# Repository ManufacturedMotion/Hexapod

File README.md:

# Hex

Hex is a six legged OpenSource Hexapod designed to serve as a moving platform for you to tinker with and build on top of! We are currently working on the third generation of the platform, Hex3.

If you're interested in learning more about the project, [visit our wiki!](https://github.com/ManufacturedMotion/Hexapod/wiki). If you want to build your own or join the community, check out our [Hex Discord](https://discord.gg/v3bbvRtFUr).

To find out info on what we're planning to change, [checkout our GitHub issues!](https://github.com/ManufacturedMotion/Hexapod/issues).

## Generations

### Hex1

- [Overview](https://github.com/ManufacturedMotion/Hexapod/wiki#mk1)
- Completed: July 2023 - May 2024
- MIT LICENSE

### Hex2
- [Overview](https://github.com/ManufacturedMotion/Hexapod/wiki#mk2)
- Completed: May 2024 - July 2025
- MIT LICENSE

### Hex3
- In-Progress: July 2025 - Present
- GNU GENERAL PUBLIC LICENSE V3

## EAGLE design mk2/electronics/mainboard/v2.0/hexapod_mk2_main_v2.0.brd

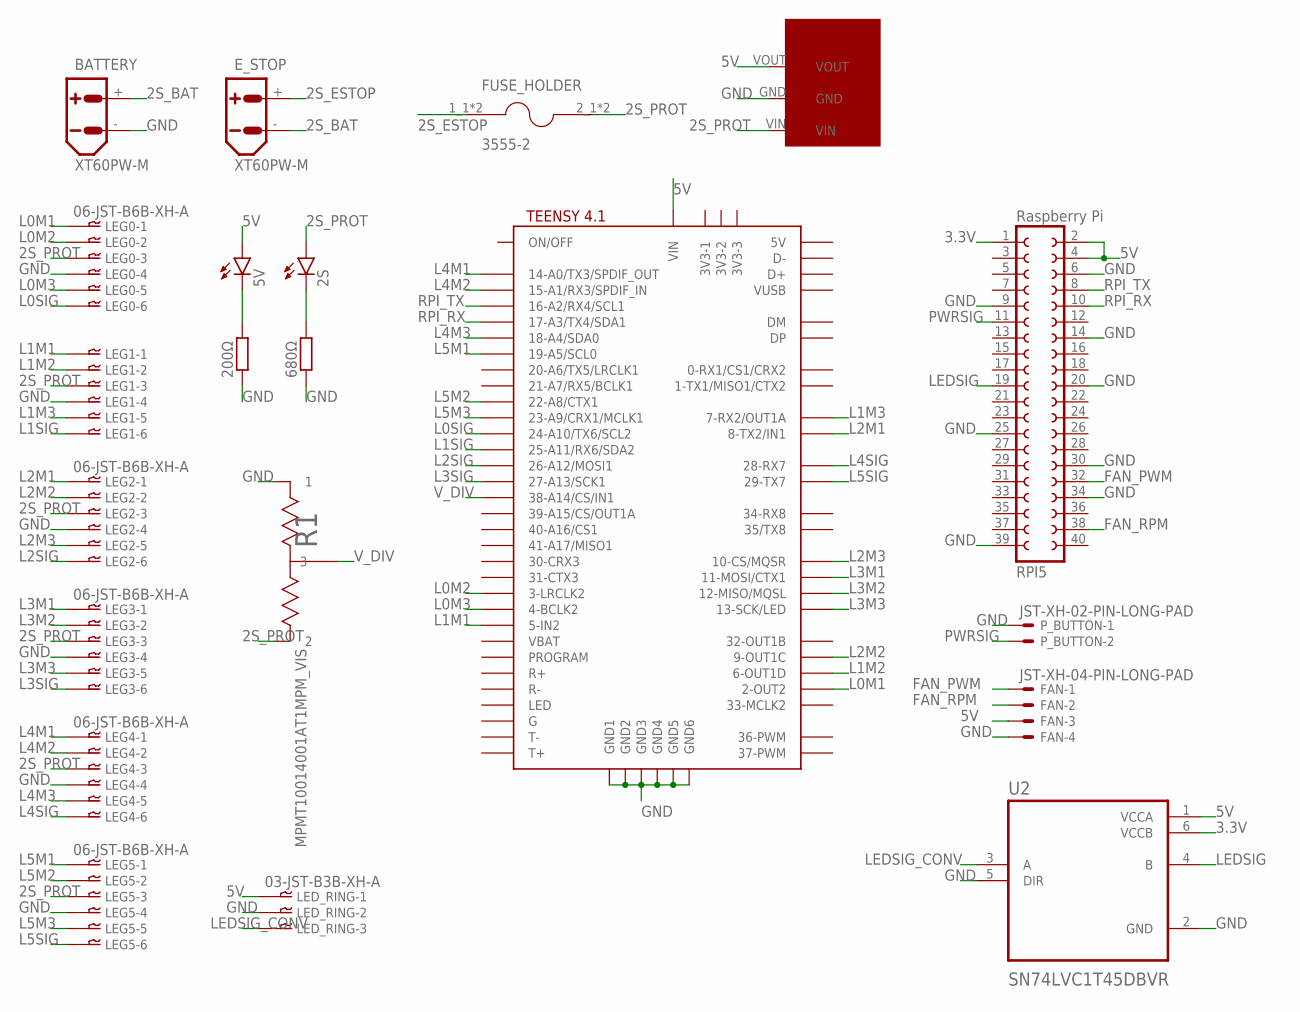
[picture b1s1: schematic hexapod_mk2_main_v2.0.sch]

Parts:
2S, 5V: LEDCHIPLED_0805; CHIPLED_0805
200Ω, 680Ω: R-EU_R0805; R0805
BATTERY: XT60PW-M
DFR0753: DFR0753
E_STOP: XT60PW-M
FAN: JST-XH-04-PIN-LONG-PAD; JST-XH-04-PACKAGE-LONG-PAD
FUSE_HOLDER: 3555-2; FUSE_3555-2
LED_RING: 03-JST-B3B-XH-A; B3B-XH
LEG0, LEG1, LEG2, LEG3, LEG4, LEG5: 06-JST-B6B-XH-A; B6B-XH
P_BUTTON: JST-XH-02-PIN-LONG-PAD; JST-XH-02-PACKAGE-LONG-PAD
R1: MPMT10014001AT1MPM_VIS; MPM_VIS
RPI5: Raspberry Pi; FE20-2
U2: SN74LVC1T45DBVR; SOT95P280X145-6N
U$1: TEENSY41

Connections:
2S_BAT: BATTERY.+, E_STOP.-
2S_ESTOP: E_STOP.+, FUSE_HOLDER.1_1 (1), FUSE_HOLDER.1_2 (1)
2S_PROT: 2S.A, DFR0753.VIN, FUSE_HOLDER.2_1 (2), FUSE_HOLDER.2_2 (2), LEG0.P$3, LEG1.P$3, LEG2.P$3, LEG3.P$3, LEG4.P$3, LEG5.P$3, R1.2
3.3V: RPI5.1, U2.6 (VCCB)
5V: 5V.A, DFR0753.VOUT, FAN.3, LED_RING.P$1, RPI5.2, RPI5.4, U2.1 (VCCA), U$1.VIN
FAN_PWM: FAN.1, RPI5.32
FAN_RPM: FAN.2, RPI5.38
GND: 200Ω.1, 680Ω.1, BATTERY.-, DFR0753.GND, FAN.4, LED_RING.P$2, LEG0.P$4, LEG1.P$4, LEG2.P$4, LEG3.P$4, LEG4.P$4, LEG5.P$4, P_BUTTON.1, R1.1, RPI5.6, RPI5.9, RPI5.14, RPI5.20, RPI5.25, RPI5.30, RPI5.34, RPI5.39, U2.2 (GND), U2.5 (DIR), U$1.GND1, U$1.GND2, U$1.GND3, U$1.GND4, U$1.GND5, U$1.GND6
L0M1: LEG0.P$1, U$1.2-OUT2
L0M2: LEG0.P$2, U$1.3-LRCLK2
L0M3: LEG0.P$5, U$1.4-BCLK2
L0SIG: LEG0.P$6, U$1.24-A10/TX6/SCL2
L1M1: LEG1.P$1, U$1.5-IN2
L1M2: LEG1.P$2, U$1.6-OUT1D
L1M3: LEG1.P$5, U$1.7-RX2/OUT1A
L1SIG: LEG1.P$6, U$1.25-A11/RX6/SDA2
L2M1: LEG2.P$1, U$1.8-TX2/IN2 (8-TX2/IN1)
L2M2: LEG2.P$2, U$1.9-OUT1C
L2M3: LEG2.P$5, U$1.10-CS\MQSR (10-CS/MQSR)
L2SIG: LEG2.P$6, U$1.26-A12/MOSI1
L3M1: LEG3.P$1, U$1.11-MOSI/CTX1
L3M2: LEG3.P$2, U$1.12-MISO/MQSL
L3M3: LEG3.P$5, U$1.13-SCK/LED
L3SIG: LEG3.P$6, U$1.27-A13/SCK1
L4M1: LEG4.P$1, U$1.14-A0/TX3/SPDIF_OUT
L4M2: LEG4.P$2, U$1.15-A1/RX3/SPDIF_IN
L4M3: LEG4.P$5, U$1.18-A4/SDA0
L4SIG: LEG4.P$6, U$1.28-RX7
L5M1: LEG5.P$1, U$1.19-A5/SCL0
L5M2: LEG5.P$2, U$1.22-A8/CTX1
L5M3: LEG5.P$5, U$1.23-A9/CRX1/MCLK1
L5SIG: LEG5.P$6, U$1.29-TX7
LEDSIG: RPI5.19, U2.4 (B)
LEDSIG_CONV: LED_RING.P$3, U2.3 (A)
unnamed: 5V.C, 200Ω.2
unnamed: 2S.C, 680Ω.2
PWRSIG: P_BUTTON.2, RPI5.11
RPI_RX: RPI5.10, U$1.17-A3/TX4/SDA1
RPI_TX: RPI5.8, U$1.16-A2/RX4/SCL1
V_DIV: R1.3, U$1.38-A14/CS/IN1

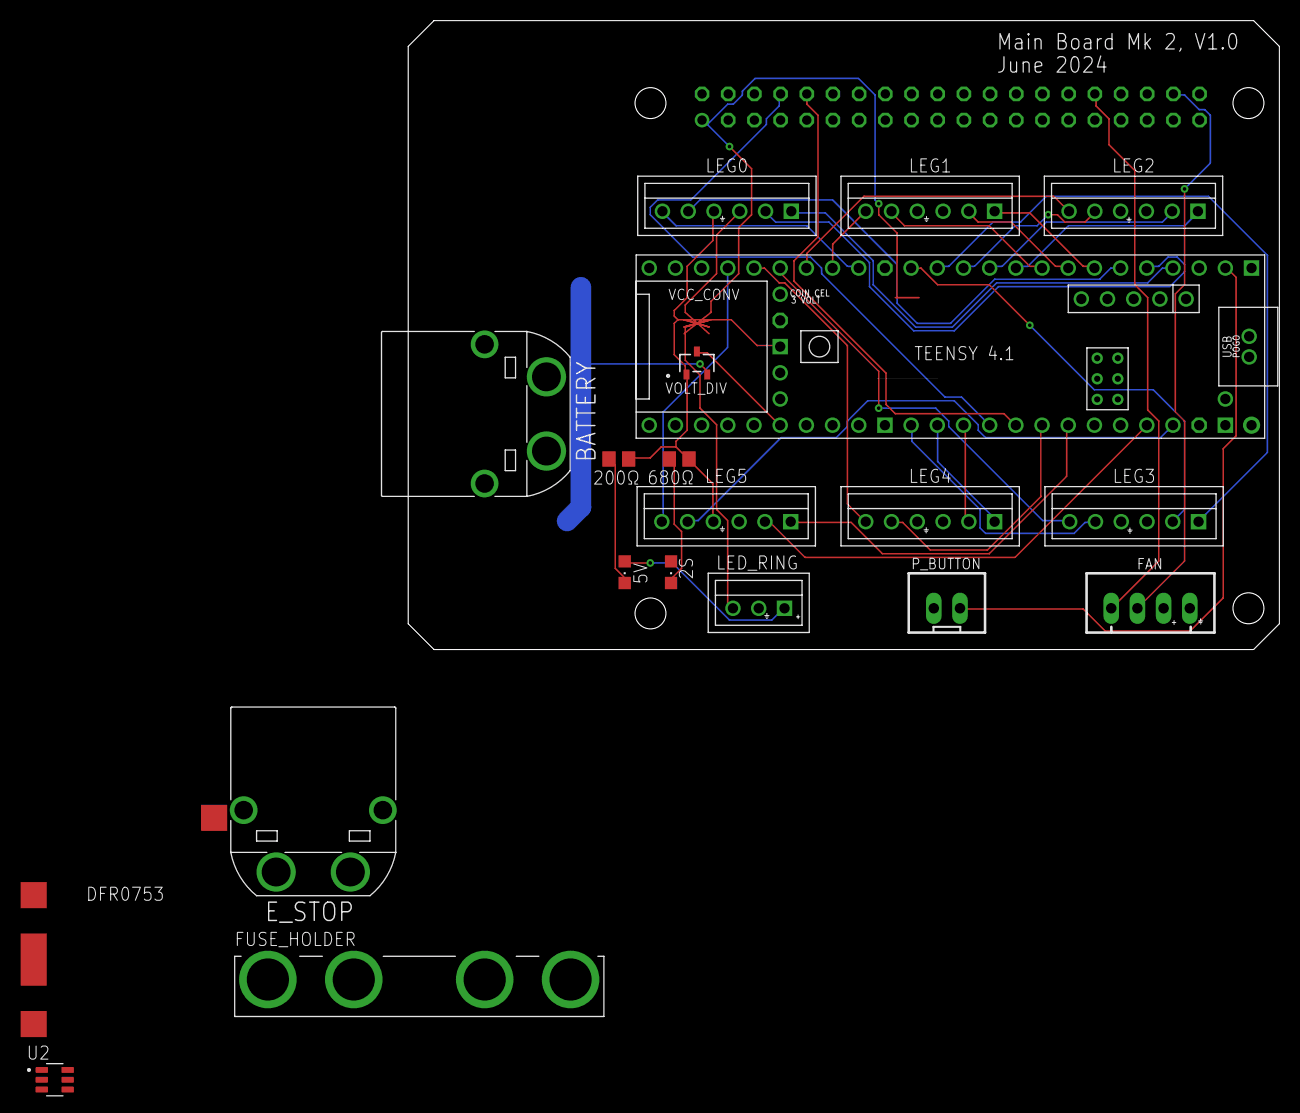
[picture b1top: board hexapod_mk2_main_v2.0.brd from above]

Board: 4 copper layers, 84.5 x 61.0 mm, 21 parts (1 on the bottom side), 40 nets.

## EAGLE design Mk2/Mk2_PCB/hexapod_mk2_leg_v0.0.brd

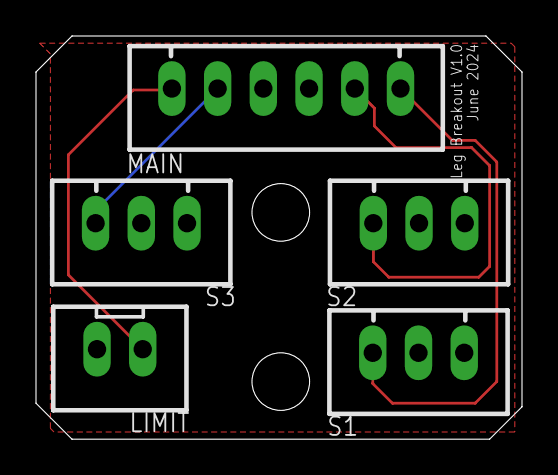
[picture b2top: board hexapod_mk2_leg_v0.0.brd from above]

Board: 2 copper layers, 27.0 x 22.4 mm, 5 parts (0 on the bottom side), 6 nets.

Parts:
LIMIT: JST-XH-02-PIN-LONG-PAD; JST-XH-02-PACKAGE-LONG-PAD
MAIN: JST-XH-06-PIN-LONG-PAD; JST-XH-06-PACKAGE-LONG-PAD
S1, S2, S3: JST-XH-03-PIN-LONG-PAD; JST-XH-03-PACKAGE-LONG-PAD

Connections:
5V: MAIN.3, S1.2, S2.2, S3.2
GND: LIMIT.2, MAIN.4, S1.1, S2.1, S3.1
LIMIT: LIMIT.1, MAIN.6
S1SIG: MAIN.1, S1.3
S2SIG: MAIN.2, S2.3
S3SIG: MAIN.5, S3.3

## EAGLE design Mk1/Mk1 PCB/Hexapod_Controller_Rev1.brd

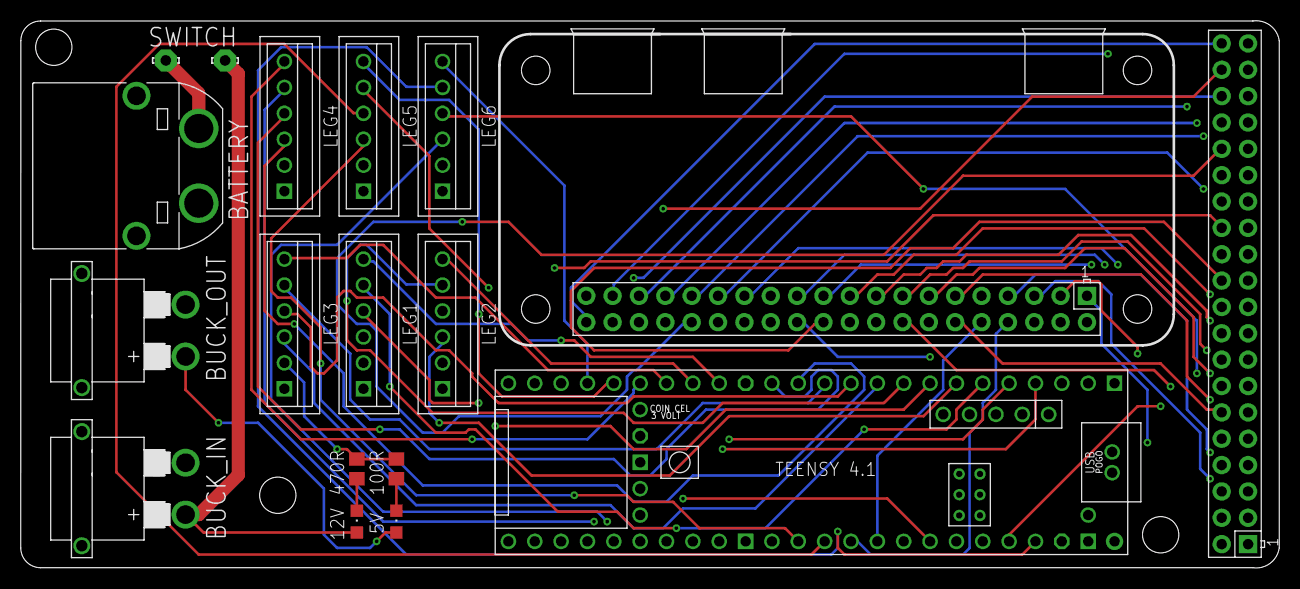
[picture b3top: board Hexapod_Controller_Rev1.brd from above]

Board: 4 copper layers, 121.3 x 52.7 mm, 18 parts (0 on the bottom side), 60 nets.

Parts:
5V, 12V: CHIPLED_0805
100R, 470R: R0805
BATTERY: XT60PW-M
BUCK_IN: XT30PW-M
BUCK_OUT: XT30PW-M
LEG1, LEG2, LEG3, LEG4, LEG5, LEG6: 06-JST-B6B-XH-A; B6B-XH
LSP1, LSP2: LSP10
U$1: TEENSY41
U$2, U$3: RPI-ZERO; RASPBERRYPI_BASTELSTUBE_V13_RASPI_BOARD_B+_FULL

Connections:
3V3: U$2.1, U$3.1
3V3_2: U$2.17, U$3.17
5V: 5V.A, BUCK_OUT.+, LEG1.P$1, LEG2.P$1, LEG3.P$1, LEG4.P$1, LEG5.P$1, LEG6.P$1, U$1.VIN, U$2.2, U$2.4, U$3.2, U$3.4
12V: 12V.A, BUCK_IN.+, LSP2.MP
12V_PRE: BATTERY.+, LSP1.MP
GND: 100R.1, 470R.1, BATTERY.-, BUCK_IN.-, BUCK_OUT.-, LEG1.P$2, LEG2.P$2, LEG3.P$2, LEG4.P$2, LEG5.P$2, LEG6.P$2, U$1.GND1, U$1.GND2, U$1.GND3, U$1.GND4, U$1.GND5, U$1.GND6, U$2.6, U$2.9, U$2.14, U$2.20, U$2.25, U$2.30, U$2.34, U$2.39, U$3.6, U$3.9, U$3.14, U$3.20, U$3.25, U$3.30, U$3.34, U$3.39
GPIO2: U$2.3, U$3.3
GPIO3: U$2.5, U$3.5
GPIO4: U$2.7, U$3.7
GPIO5: U$2.29, U$3.29
GPIO6: U$2.31, U$3.31
GPIO7: U$2.26, U$3.26
GPIO8: U$2.24, U$3.24
GPIO9: U$2.21, U$3.21
GPIO10: U$2.19, U$3.19
GPIO11: U$2.23, U$3.23
GPIO12: U$2.32, U$3.32
GPIO13: U$2.33, U$3.33
GPIO16: U$2.36, U$3.36
GPIO17: U$2.11, U$3.11
GPIO18: U$2.12, U$3.12
GPIO19: U$2.35, U$3.35
GPIO20: U$2.38, U$3.38
GPIO21: U$2.40, U$3.40
GPIO22: U$2.15, U$3.15
GPIO23: U$2.16, U$3.16
GPIO24: U$2.18, U$3.18
GPIO25: U$2.22, U$3.22
GPIO26: U$2.37, U$3.37
GPIO27: U$2.13, U$3.13
ID_SC: U$2.28, U$3.28
ID_SD: U$2.27, U$3.27
L1M1: LEG1.P$3, U$1.2-OUT2
L1M2: LEG1.P$4, U$1.3-LRCLK2
L1M3: LEG1.P$5, U$1.4-BCLK2
L1SIG: LEG1.P$6, U$1.24-A10/TX6/SCL2
L2M1: LEG2.P$3, U$1.5-IN2
L2M2: LEG2.P$4, U$1.6-OUT1D
L2M3: LEG2.P$5, U$1.7-RX2/OUT1A
L2SIG: LEG2.P$6, U$1.25-A11/RX6/SDA2
L3M1: LEG3.P$3, U$1.8-TX2/IN2
L3M2: LEG3.P$4, U$1.9-OUT1C
L3M3: LEG3.P$5, U$1.10-CS\MQSR
L3SIG: LEG3.P$6, U$1.26-A12/MOSI1
L4M1: LEG4.P$3, U$1.11-MOSI/CTX1
L4M2: LEG4.P$4, U$1.12-MISO/MQSL
L4M3: LEG4.P$5, U$1.13-SCK/LED
L4SIG: LEG4.P$6, U$1.27-A13/SCK1
L5M1: LEG5.P$3, U$1.14-A0/TX3/SPDIF_OUT
L5M2: LEG5.P$4, U$1.15-A1/RX3/SPDIF_IN
L5M3: LEG5.P$5, U$1.18-A4/SDA0
L5SIG: LEG5.P$6, U$1.28-RX7
L6M1: LEG6.P$3, U$1.19-A5/SCL0
L6M2: LEG6.P$4, U$1.22-A8/CTX1
L6M3: LEG6.P$5, U$1.23-A9/CRX1/MCLK1
L6SIG: LEG6.P$6, U$1.29-TX7
unnamed: 5V.C, 100R.2
unnamed: 12V.C, 470R.2
RPI_RX: U$1.17-A3/TX4/SDA1, U$2.10
RPI_TX: U$1.16-A2/RX4/SCL1, U$2.8

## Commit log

2023-11-12 First files
2023-11-12 add initial BOM
2023-11-12 add checkbox
2023-11-12 remove checkbox
2023-11-28 Update BOMs
2024-01-08 add ik first pass
2024-02-04 Rename HexapodController/basic_18servo_control.ino to HexapodController/basic_18servo_control/basic_18servo_control.ino
2024-02-04 Add PCB Design files
2024-02-04 Add in offsets
2024-02-04 fix formatting
2024-02-04 Update Offsets.md
    Danny's undefined motors
2024-02-04 Update Offsets.md
    Zack undefined motors
2024-02-06 add finalized 3d printed parts
2024-02-06 leg and axis object compatibility
2024-02-06 Update base to fit on Bambu X1C
2024-02-12 Add updated S1 Mounts
2024-02-13 Add files via upload
    refactor variable & function names as per project standards. Update config to use macros for defining user specific values.
2024-02-13 Delete HexapodController/HexapodController.h
    artifact after file rename
2024-02-13 Delete HexapodController/config.cpp
    no longer needed after refactor for macros
2024-02-13 Changes for successful code compilation
2024-02-14 update S1 mount
2024-02-14 fix min pos typo
2024-02-14 update image relative link
2024-02-14 Swap out logo for Hexapod Logo
2024-02-15 Update config.hpp
    swap software definitions of legs 2 & 3 because PCB makes it confusing.
2024-02-15 Update config.hpp
    need to also change user offsets to match new software definitions
2024-02-15 Update config.hpp
    rotate first 3 motor definitions. 1 -> 2, 2 -> 3, 3 -> 1
2024-02-28 Reorganize
2024-02-28 Reorganize for easer arduino dev
2024-02-28 add new 3D printed files
2024-02-29 Update config.hpp
    Revert the change
2024-02-29 Revert "Update .gitmodules"
2024-02-29 Revert "Revert "Update .gitmodules""
2024-03-08 Add in measurements for leg motors
2024-03-09 Add in Rpi Serial Passthrough
2024-03-23 update serial example
2024-03-25 Add in web interface
2024-03-25 update documentation
2024-03-26 Add controller testing code
2024-04-03 Properly handle controller input
2024-04-04 Add updated webserver
2024-04-04 Fix Serial output
2024-04-09 Update main.py
    add space to start of serial commands. Required to match how data is sent from serial monitor
2024-04-09 Update main.py
    1 space was working before but then stopped... 2 spaces seemed to fix??
2024-04-14 Update serial send for reliability
2024-05-05 Add in G0 from the controller
2024-05-09 handle macros
2024-05-14 Add in controller join after start
2024-05-17 update pollrate
2024-05-17 Prepare for Mark2
2024-05-25 Rename L1,3,4,5 - S1 Motor Mount - Final.stl to L2,3,4,5 - S1 Motor Mount - Final.stl
2024-06-04 Rough draft of PCB rev 2
2024-06-04 Draft2 of Mk2 PCB
2024-06-14 Mk1 cleanup + PCB revisions
2024-06-19 Update Mk2 Schematic
2024-06-21 Add leg breakout PCB
2024-06-22 Finalized main PCB
2024-06-22 update leg pcb
2024-06-22 add board revision to pcb
2024-06-22 Add files via upload
    add 2 color logo file
2024-06-22 add logo bitmap
2024-06-22 crop bitmap
2024-06-23 board update
2024-06-23 remove webserver dependency
2024-06-23 auto route main board. add silkscreens to both
2024-06-23 docker first pass w/ controller
2024-06-23 Restructure code for merger with HexpodController
2024-06-23 fix autorouting issues
2024-06-23 fix folder structure
2024-06-23 reorient main pcb label
2024-06-23 fix leg pcb label
2024-06-23 update file hierarchy
2024-06-23 first pass, build success, operation untested
2024-06-23 testing naming resolution
2024-06-23 Fix naming mismatch
2024-06-23 remove dummy folder
2024-06-24 Add PCB Gerber Files
2024-06-25 Add electronics BOM
2024-06-25 Add viewable format
2024-06-25 take 2 at viewable BOM
2024-07-13 Add in HexapodController, in a somewhat portable way
2024-07-13 Remove unused variable
2024-07-13 Refactor container and add container readme
2024-07-29 Update docker-compose-dev.yml
    old script did not exist - docker container immediately exited
2024-07-29 working skeleton for publisher and listener nodes
2024-08-02 give executable permissions
2024-08-02 add python imports for led experiments
2024-08-20 add draft cad
2024-08-27 add new cad assembly:
2024-08-31 trying to pass serial to container
2024-09-01 puzzle piece assembly
2024-09-01 pyserial access granted
2024-09-14 best I can do
2024-09-18 minor CAD revisions
2024-09-22 working code cleanup branch
2024-09-25 2024-07-24_assembly
2024-10-07 fix Dillon's motor offsets for Mk2 build
2024-10-12 low-level gcode on G*
2024-10-13 Working model runner
2024-10-13 fix gitignore file
2024-11-06 CAD improvements and heatset guide
2024-11-18 add sit function
2024-11-19 add led code
2024-11-19 Update config.hpp
    revert changes to Danny's config
2024-11-23 update images
2024-11-23 pushbutton shutdown initial commit
2024-11-23 setup script to update crontab
2024-11-23 Update setup.sh
    remove debug print
2024-11-23 Update setup.sh
    make cron-out dir
2024-11-23 Update setup.sh
    fix for back to back runs
2024-11-23 Update setup.sh
    auto install required package
2024-11-23 first pass
2024-11-24 pcb board layout
2024-11-24 worth testing
2024-11-24 fix board sever
2024-11-24 update for new ubuntu version
2024-11-24 update setup script again
2024-11-24 Update setup.sh
    remove user interaction
2024-11-24 add vsense logic to main
2024-11-25 Remove old backups for space
2024-11-25 Remove .DS_Store files from repository
2024-11-25 add dsstore files to git ignore
2024-11-25 remove DS store files
2024-11-26 finalized pcb
2024-11-26 teleop continuation
2024-12-28 update CAD
2024-12-29 update Brace mounting
2025-01-13 update setup script and readme
2025-01-17 ordered
2025-01-20 update BOM
2025-02-01 CAD Revisions
2025-02-02 remove unused code
2025-02-14 Update setup.sh
    remove comment for Danny
2025-02-14 Update setup.sh
    remove other comment
2025-02-16 initial commit for voltage reading noise filtering
2025-02-16 sit on startup
2025-02-16 use G2 to send up to 18 motor positions
2025-02-16 Update main.cpp
    add question TODO
2025-02-16 updates to sit and moveToPosAtSpeed
2025-02-16 Update json_joints.cpp
    recapitalize 1st key in json
2025-02-17 fix LED install
2025-02-19 add initial controller support
2025-02-19 remove logs
2025-02-20 small changes
2025-02-21 parsing looking good. P0/P2 working. bug with moveToPosAtSpeed
2025-02-21 remove wait var in parsing code. was not used
2025-02-21 fix hexapod obj references. P1 and moveToPosAtSpeed now fixed
2025-02-21 remove debug stuff and small syntax changes
2025-02-21 bug fixes
2025-02-22 final touches
2025-02-22 final touches for real
2025-02-22 Update main.cpp
    add startup back to main
2025-02-25 controller improvements
2025-02-26 fix controller and gitignore files
2025-02-26 update git ignore
2025-02-27 new gait package & node for Twist -> json cmd. Update teensy node
2025-02-27 add X button as move to neutral pos
2025-02-28 correct offsets
2025-03-01 updates for step combination
2025-03-01 fix for legEnqueue function calls
2025-03-01 comment and serial changes
2025-03-01 newline when writing to teensy to avoid msg concatenation
2025-03-01 more changes to prevent msg concatenation. fine tuning of timer & step size values
2025-03-02 move LED setup to Dockerfile
2025-03-02 Switch LEDs based on button press
2025-03-02 final adjustment
2025-03-03 add color changing button
2025-03-04 try joystick implementation
2025-03-04 finish joystick functionality
2025-03-08 fine tune walking and scale speed on joystick
2025-03-08 remove unused resources. stop double scaling speed
2025-03-08 update zeros
2025-03-10 add rqt support
2025-03-11 display
2025-03-11 more display updates
2025-03-11 update display code
2025-03-12 Update README.md
    shorten readme and point to the wiki
2025-03-19 update Lid
2025-03-21 add launch for walking commands
2025-03-22 update LED functionality
2025-03-22 update config
2025-03-22 update offset
2025-03-22 Create Images
2025-03-22 Create temp
2025-03-22 Add files via upload
    add mk1 photos
2025-03-22 update offsets
2025-03-23 misc fixes
2025-03-23 add tune cmd and parsing safety nets
2025-03-23 remove debug print from Danny
2025-03-24 grab ros2 node graph from pi
2025-03-24 Delete mk2/code/real_time/teensy_code/lib/HexapodController/README.md
    remove readme file
2025-03-30 gait fixes
2025-04-19 *untested* refactor logging to go through a serial handler class
2025-04-19 move hexapod.cpp optional logging behind preprocessor. Make voltagemonitor code use new serial handler class
2025-04-21 add WIP. need to discuss with others
2025-04-21 add script for sending txt file contents to teensy
2025-04-22 support a sleep/delay cmd in txt file. add example txt file for testing
2025-04-22 tested on robot
2025-04-29 remove gcode support. put json code inside serial parser file and do cleanup
2025-05-04 Redesign gait for optimal stepping
2025-05-04 fix definitions for log levels. User to define log level in user_config.hpp
2025-05-04 don't know where those changes came from. removing files
2025-05-05 minor bugfixes
2025-05-05 add step queuing method
2025-05-05 fix merge conflicts
2025-05-05 updates for pi to wait before sending next cmd
2025-05-05 update gait code
2025-05-05 have presets send a time ack
2025-05-06 add changes for latency
2025-05-07 this is much smoother. just need to test on bot and fix issue where sending duplicate msgs
2025-05-07 added ack variable. changed speed scaling
2025-05-07 add option to disengage servos
2025-05-07 only try to parse json commands
2025-05-07 final tweaks after testing
2025-05-07 Revert "Move time updates"
2025-05-07 blank commit to open PR
2025-05-09 add parsing
2025-05-09 attempt to disengage servos
2025-05-13 Revert "Revert "Move time updates""
2025-05-14 disengage servo
2025-05-14 try more things
2025-05-17 return to neutral working
2025-05-20 Dillon gobilda servo calibration. Also add in missing file for log level definitions
2025-05-22 update led handling
2025-05-22 more LED updates
2025-05-26 minor improvements
2025-06-01 enable VSET command
2025-06-01 use vset and speed up serial
2025-06-08 add spare leg zero points
2025-06-19 get left joystick working
2025-06-20 finalize discrete controls
2025-06-20 add polling functionality
2025-06-23 add mag handling
2025-06-28 fix LED reference
2025-06-28 initial push
2025-06-28 working json but bad values
2025-06-28 speed based scalar for step size
2025-06-28 text to display screen
2025-06-28 small update.broken though
2025-06-28 working text updates. need to fix values
2025-06-28 ik sit stand
2025-06-29 lowpass filter
2025-06-29 update Hexapod direction
2025-06-29 working measurements
2025-06-29 lower vbat
2025-06-29 initial reboot setup
2025-06-29 add danny's new offsets
2025-06-29 servo decoupling caps
2025-07-13 new zeros after reassembly
2025-07-13 add dance command and update config
2025-07-13 map dances to buttons
2025-07-14 tune GoBilda Servos
2025-07-17 new zeros again
2025-07-17 start container on boot
2025-07-17 update display
2025-07-17 safe sit, unit queue blocking
2025-07-17 sit on shutdown
2025-07-17 try except for sit shutdown
2025-07-18 require rapid move first + tuning
2025-07-18 new dances
2025-07-18 Update start_container
2025-07-18 dance rework
2025-07-18 fix logic
2025-07-18 fix button mapping?
2025-07-18 fix joy again
2025-07-19 detach button control
2025-07-19 dance updates
2025-07-19 add detach functionality
2025-07-20 Create LICENSE
2025-07-20 fix compiler warnings
2025-07-21 remove dead code
2025-07-22 prep for submodule organization
2025-07-22 add the submodule pointers. also move the mk2 boms to new location
2025-07-22 had bad pointers. will need to test to see if this needs more changes
2025-07-22 submodules locked on respective main branches
2025-07-22 Update README.md
    fix Hex naming capitalizaion
2025-07-22 Update .gitmodules
    fix spaces
2025-07-22 update submodule pointers
2025-07-23 wrap up Hex2
2025-07-23 add _hex banner

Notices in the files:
parts and their libraries:
COPYRIGHT: Copyright (C) 2024 Ultra Librarian. All rights reserved.
